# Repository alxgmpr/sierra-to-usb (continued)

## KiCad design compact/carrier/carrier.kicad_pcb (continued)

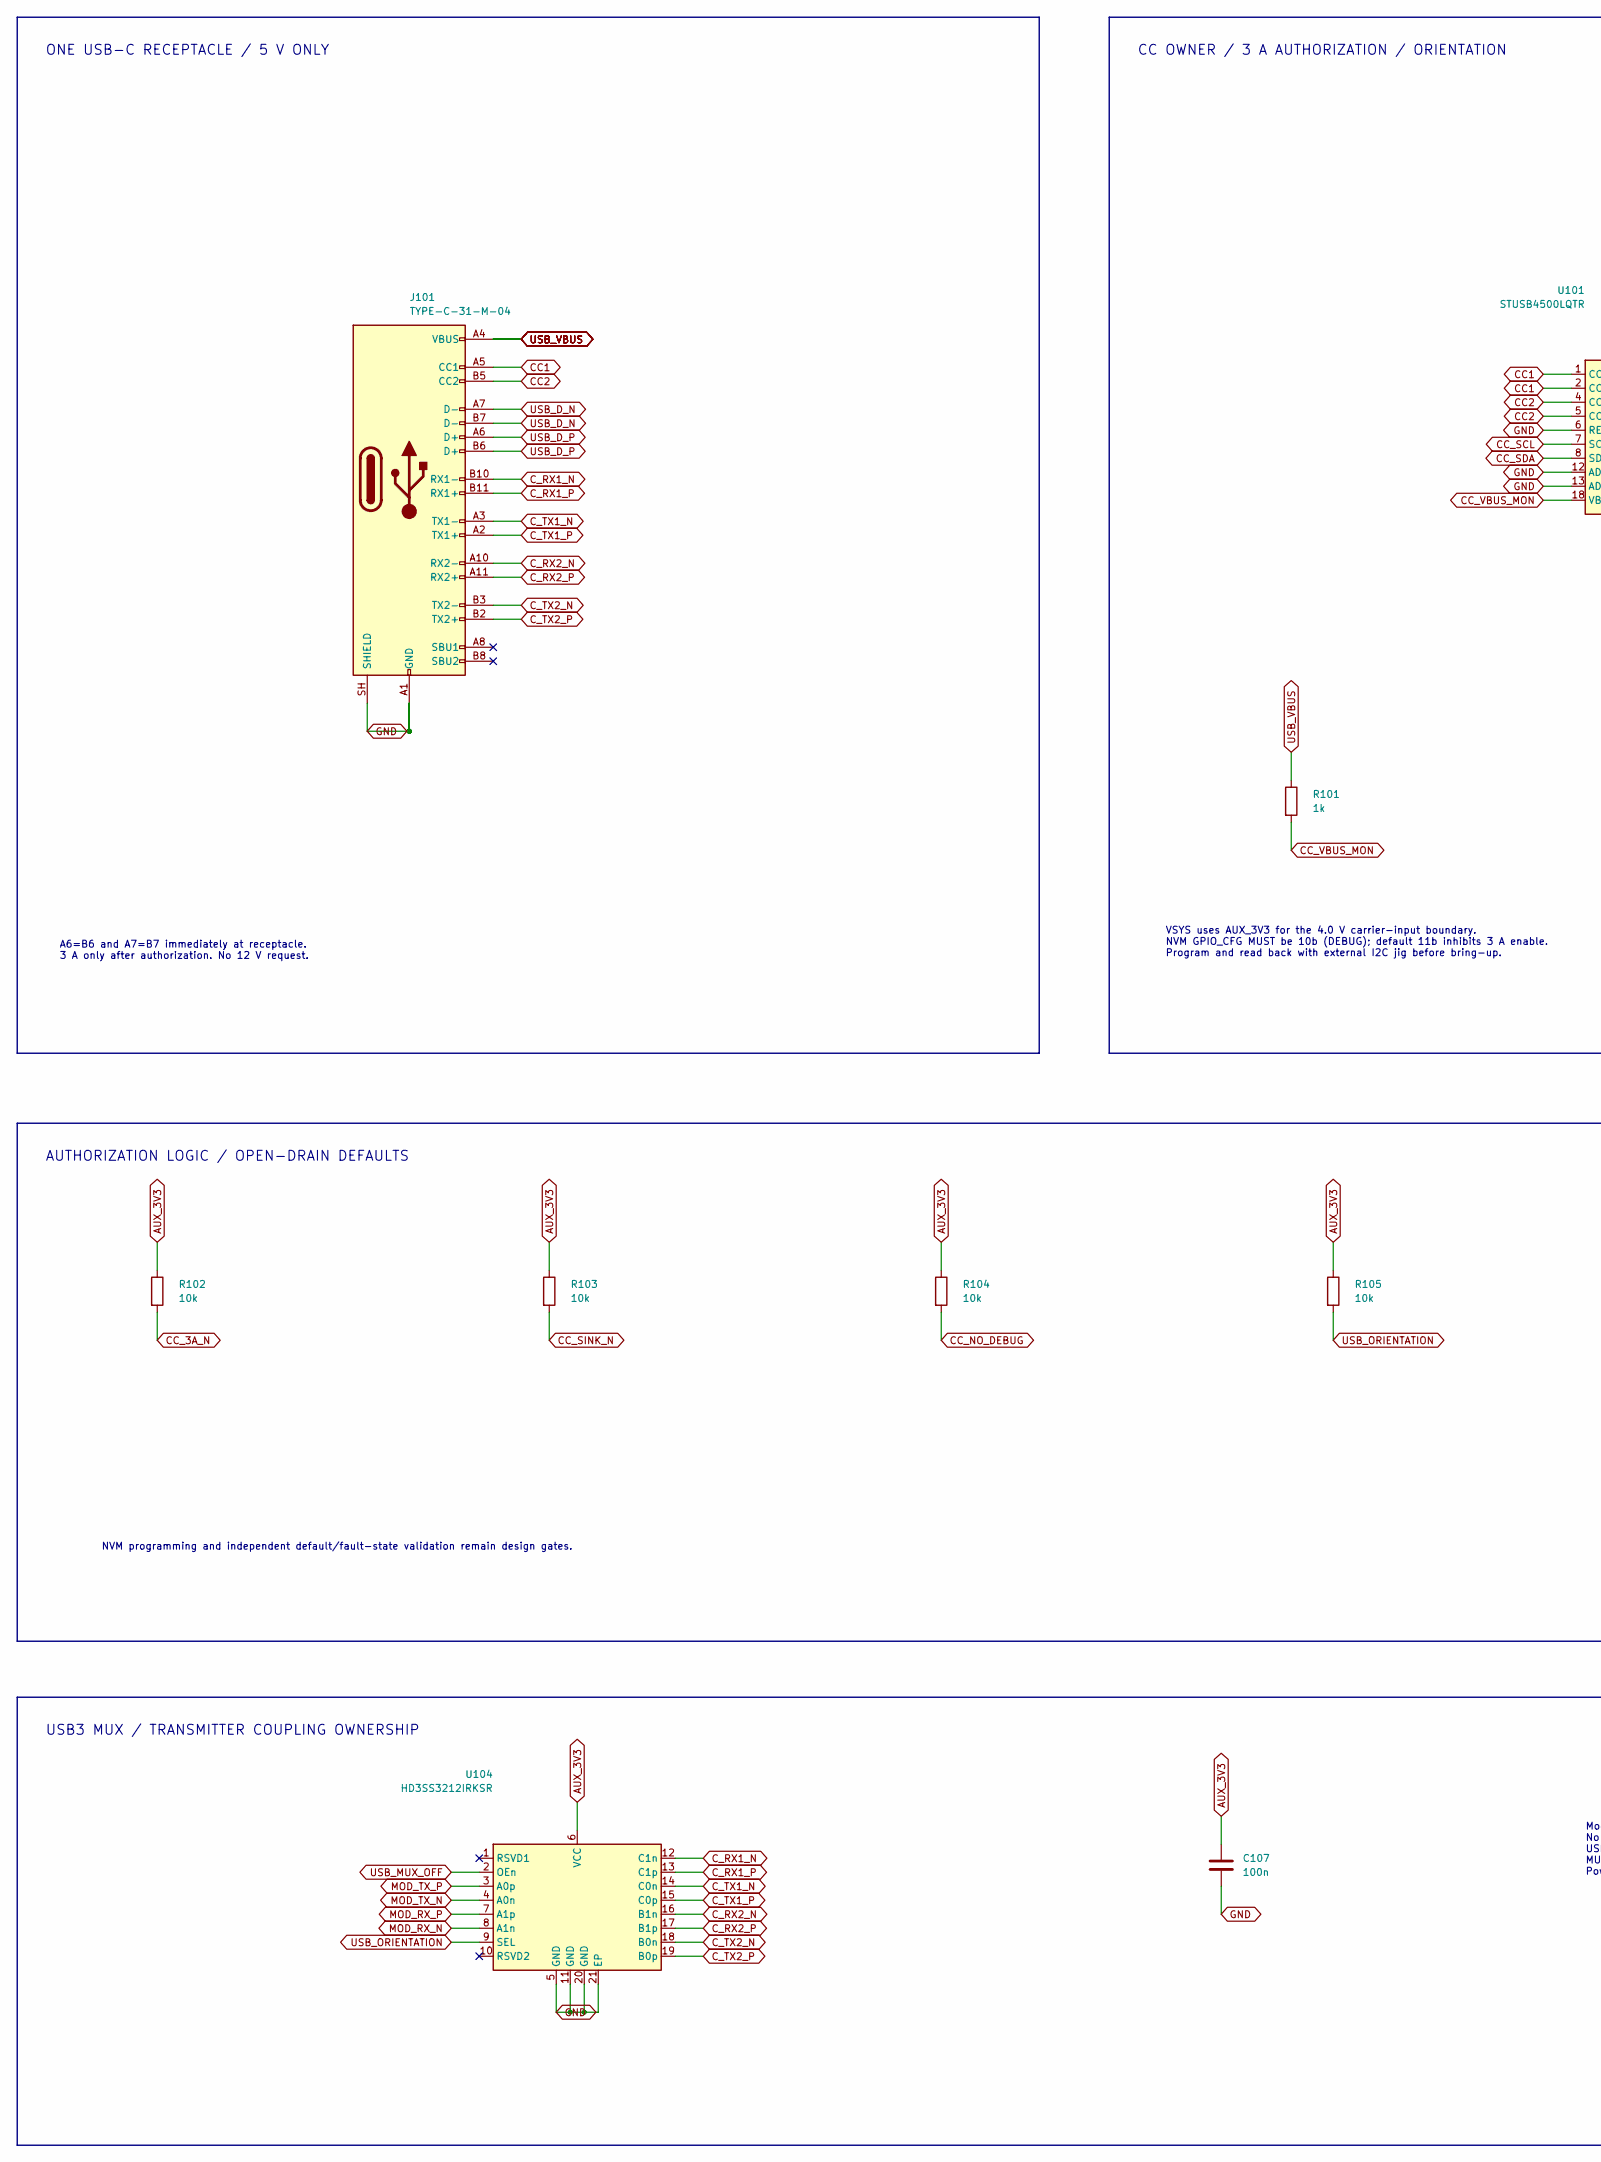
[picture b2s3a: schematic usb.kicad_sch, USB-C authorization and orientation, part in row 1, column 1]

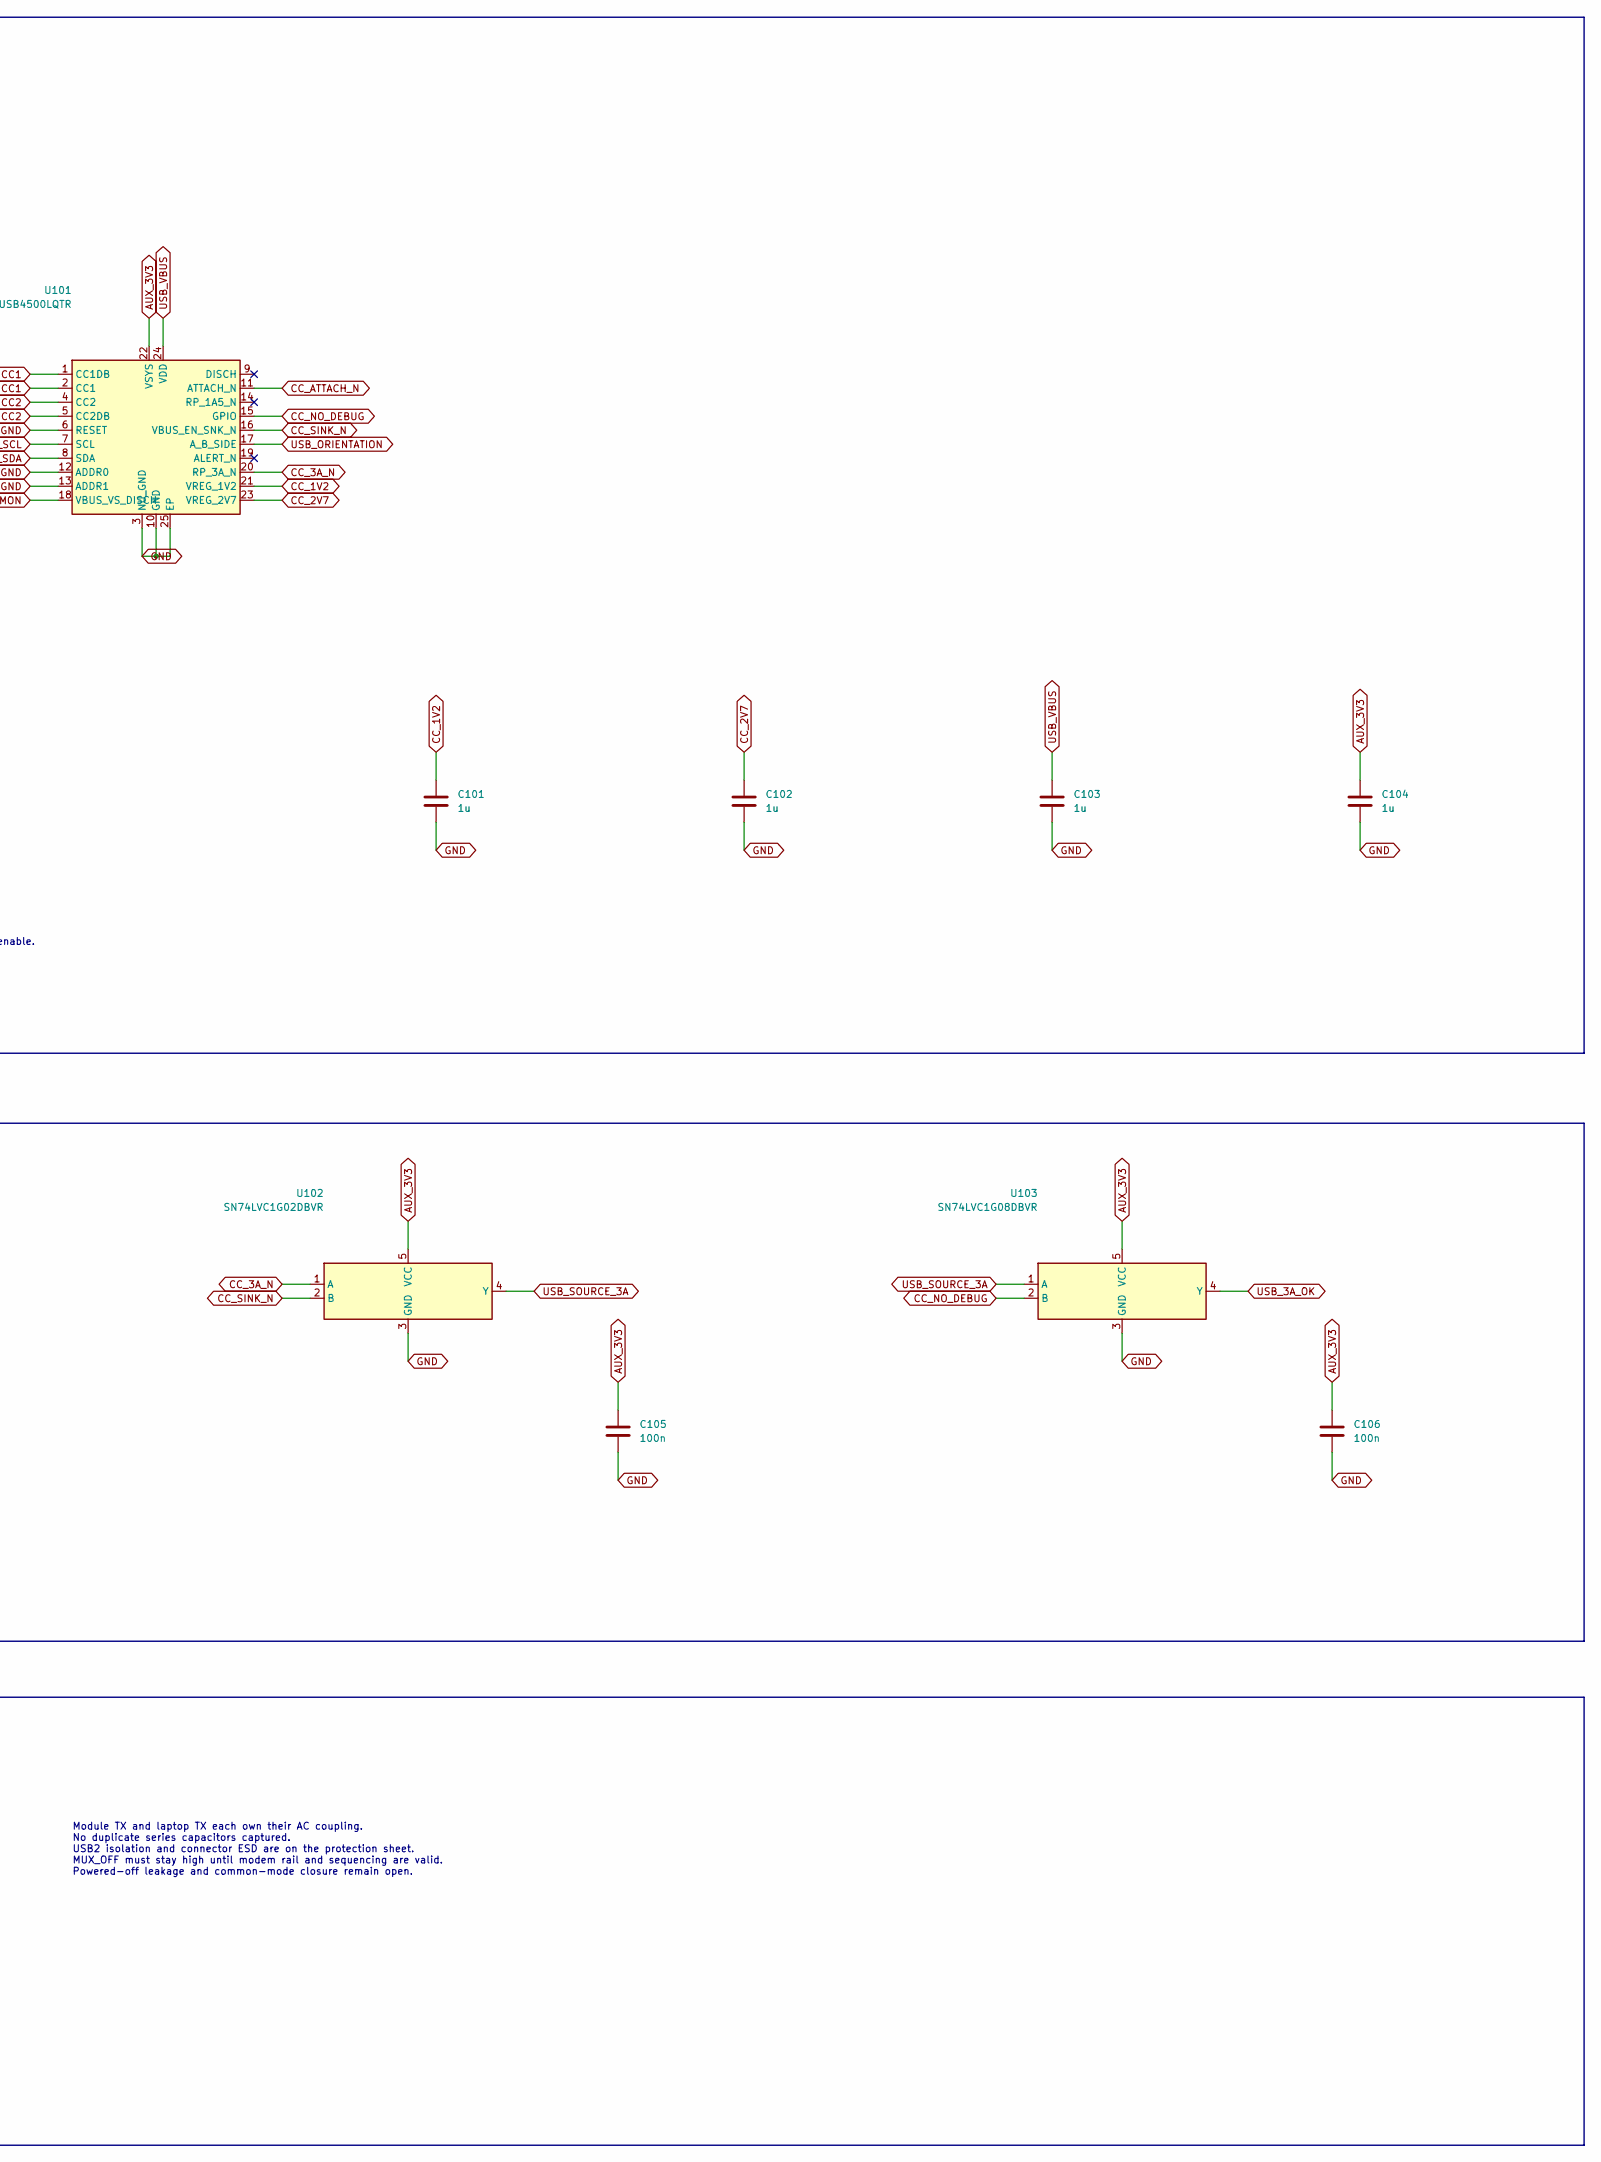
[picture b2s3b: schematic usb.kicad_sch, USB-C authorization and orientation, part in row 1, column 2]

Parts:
C101, C102, C103, C104: 1u; C_1206_3216Metric; MPN C3216X7R1H105K160AB
C105, C106, C107: 100n; C_0805_2012Metric; MPN C2012X7R1H104K085AA
J101: TYPE-C-31-M-04; USB_C_Receptacle_HRO_TYPE-C-31-M-04; MPN TYPE-C-31-M-04; LCSC C129018
R101: 1k; R_0603_1608Metric; MPN RC0603FR-071KL
R102, R103, R104, R105: 10k; R_0603_1608Metric; MPN RC0603FR-0710KL
U101: STUSB4500LQTR; QFN-24-1EP_4x4mm_P0.5mm_EP2.6x2.6mm; MPN STUSB4500LQTR
U102: SN74LVC1G02DBVR; SOT-23-5; MPN SN74LVC1G02DBVR
U103: SN74LVC1G08DBVR; SOT-23-5; MPN SN74LVC1G08DBVR
U104: HD3SS3212IRKSR; WQFN-20-1EP_2.5x4.5mm_P0.5mm_EP1x2.9mm; MPN HD3SS3212IRKSR

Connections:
AUX_3V3: C104.1, C105.1, C106.1, C107.1, R102.1, R103.1, R104.1, R105.1, U101.22 (VSYS), U102.5 (VCC), U103.5 (VCC), U104.6 (VCC); also elsewhere on the board
CC1: J101.A5 (CC1), U101.1 (CC1DB), U101.2 (CC1); also elsewhere on the board
CC2: J101.B5 (CC2), U101.4 (CC2), U101.5 (CC2DB); also elsewhere on the board
CC_1V2: C101.1, U101.21 (VREG_1V2)
CC_2V7: C102.1, U101.23 (VREG_2V7)
CC_3A_N: R102.2, U101.20 (RP_3A_N), U102.1 (A)
CC_ATTACH_N: U101.11 (ATTACH_N); also elsewhere on the board
CC_NO_DEBUG: R104.2, U101.15 (GPIO), U103.2 (B)
CC_SCL: U101.7 (SCL); also elsewhere on the board
CC_SDA: U101.8 (SDA); also elsewhere on the board
CC_SINK_N: R103.2, U101.16 (VBUS_EN_SNK_N), U102.2 (B)
CC_VBUS_MON: R101.2, U101.18 (VBUS_VS_DISCH)
C_RX1_N: J101.B10 (RX1-), U104.12 (C1n); also elsewhere on the board
C_RX1_P: J101.B11 (RX1+), U104.13 (C1p); also elsewhere on the board
C_RX2_N: J101.A10 (RX2-), U104.16 (B1n); also elsewhere on the board
C_RX2_P: J101.A11 (RX2+), U104.17 (B1p); also elsewhere on the board
C_TX1_N: J101.A3 (TX1-), U104.14 (C0n); also elsewhere on the board
C_TX1_P: J101.A2 (TX1+), U104.15 (C0p); also elsewhere on the board
C_TX2_N: J101.B3 (TX2-), U104.18 (B0n); also elsewhere on the board
C_TX2_P: J101.B2 (TX2+), U104.19 (B0p); also elsewhere on the board
GND: C101.2, C102.2, C103.2, C104.2, C105.2, C106.2, C107.2, J101.A1 (GND), J101.A12 (GND), J101.B1 (GND), J101.B12 (GND), J101.SH (SHIELD), U101.3 (NU_GND), U101.6 (RESET), U101.10 (GND), U101.12 (ADDR0), U101.13 (ADDR1), U101.25 (EP), U102.3 (GND), U103.3 (GND), U104.5 (GND), U104.11 (GND), U104.20 (GND), U104.21 (EP); also elsewhere on the board
MOD_RX_N: U104.8 (A1n); also elsewhere on the board
MOD_RX_P: U104.7 (A1p); also elsewhere on the board
MOD_TX_N: U104.4 (A0n); also elsewhere on the board
MOD_TX_P: U104.3 (A0p); also elsewhere on the board
USB_3A_OK: U103.4 (Y); also elsewhere on the board
USB_D_N: J101.A7 (D-), J101.B7 (D-); also elsewhere on the board
USB_D_P: J101.A6 (D+), J101.B6 (D+); also elsewhere on the board
USB_MUX_OFF: U104.2 (OEn); also elsewhere on the board
USB_ORIENTATION: R105.2, U101.17 (A_B_SIDE), U104.9 (SEL)
USB_SOURCE_3A: U102.4 (Y), U103.1 (A)
USB_VBUS: C103.1, J101.A4 (VBUS), J101.A9 (VBUS), J101.B4 (VBUS), J101.B9 (VBUS), R101.1, U101.24 (VDD); also elsewhere on the board

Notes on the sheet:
ONE USB-C RECEPTACLE / 5 V ONLY
A6=B6 and A7=B7 immediately at receptacle. 3 A only after authorization. No 12 V request.
CC OWNER / 3 A AUTHORIZATION / ORIENTATION
VSYS uses AUX_3V3 for the 4.0 V carrier-input boundary. NVM GPIO_CFG MUST be 10b (DEBUG); default 11b inhibits 3 A enable. Program and read back with external I2C jig before bring-up.
AUTHORIZATION LOGIC / OPEN-DRAIN DEFAULTS
NVM programming and independent default/fault-state validation remain design gates.
USB3 MUX / TRANSMITTER COUPLING OWNERSHIP
Module TX and laptop TX each own their AC coupling. No duplicate series capacitors captured. USB2 isolation and connector ESD are on the protection sheet. MUX_OFF must stay high until modem rail and sequencing are valid. Powered-off leakage and common-mode closure remain open.

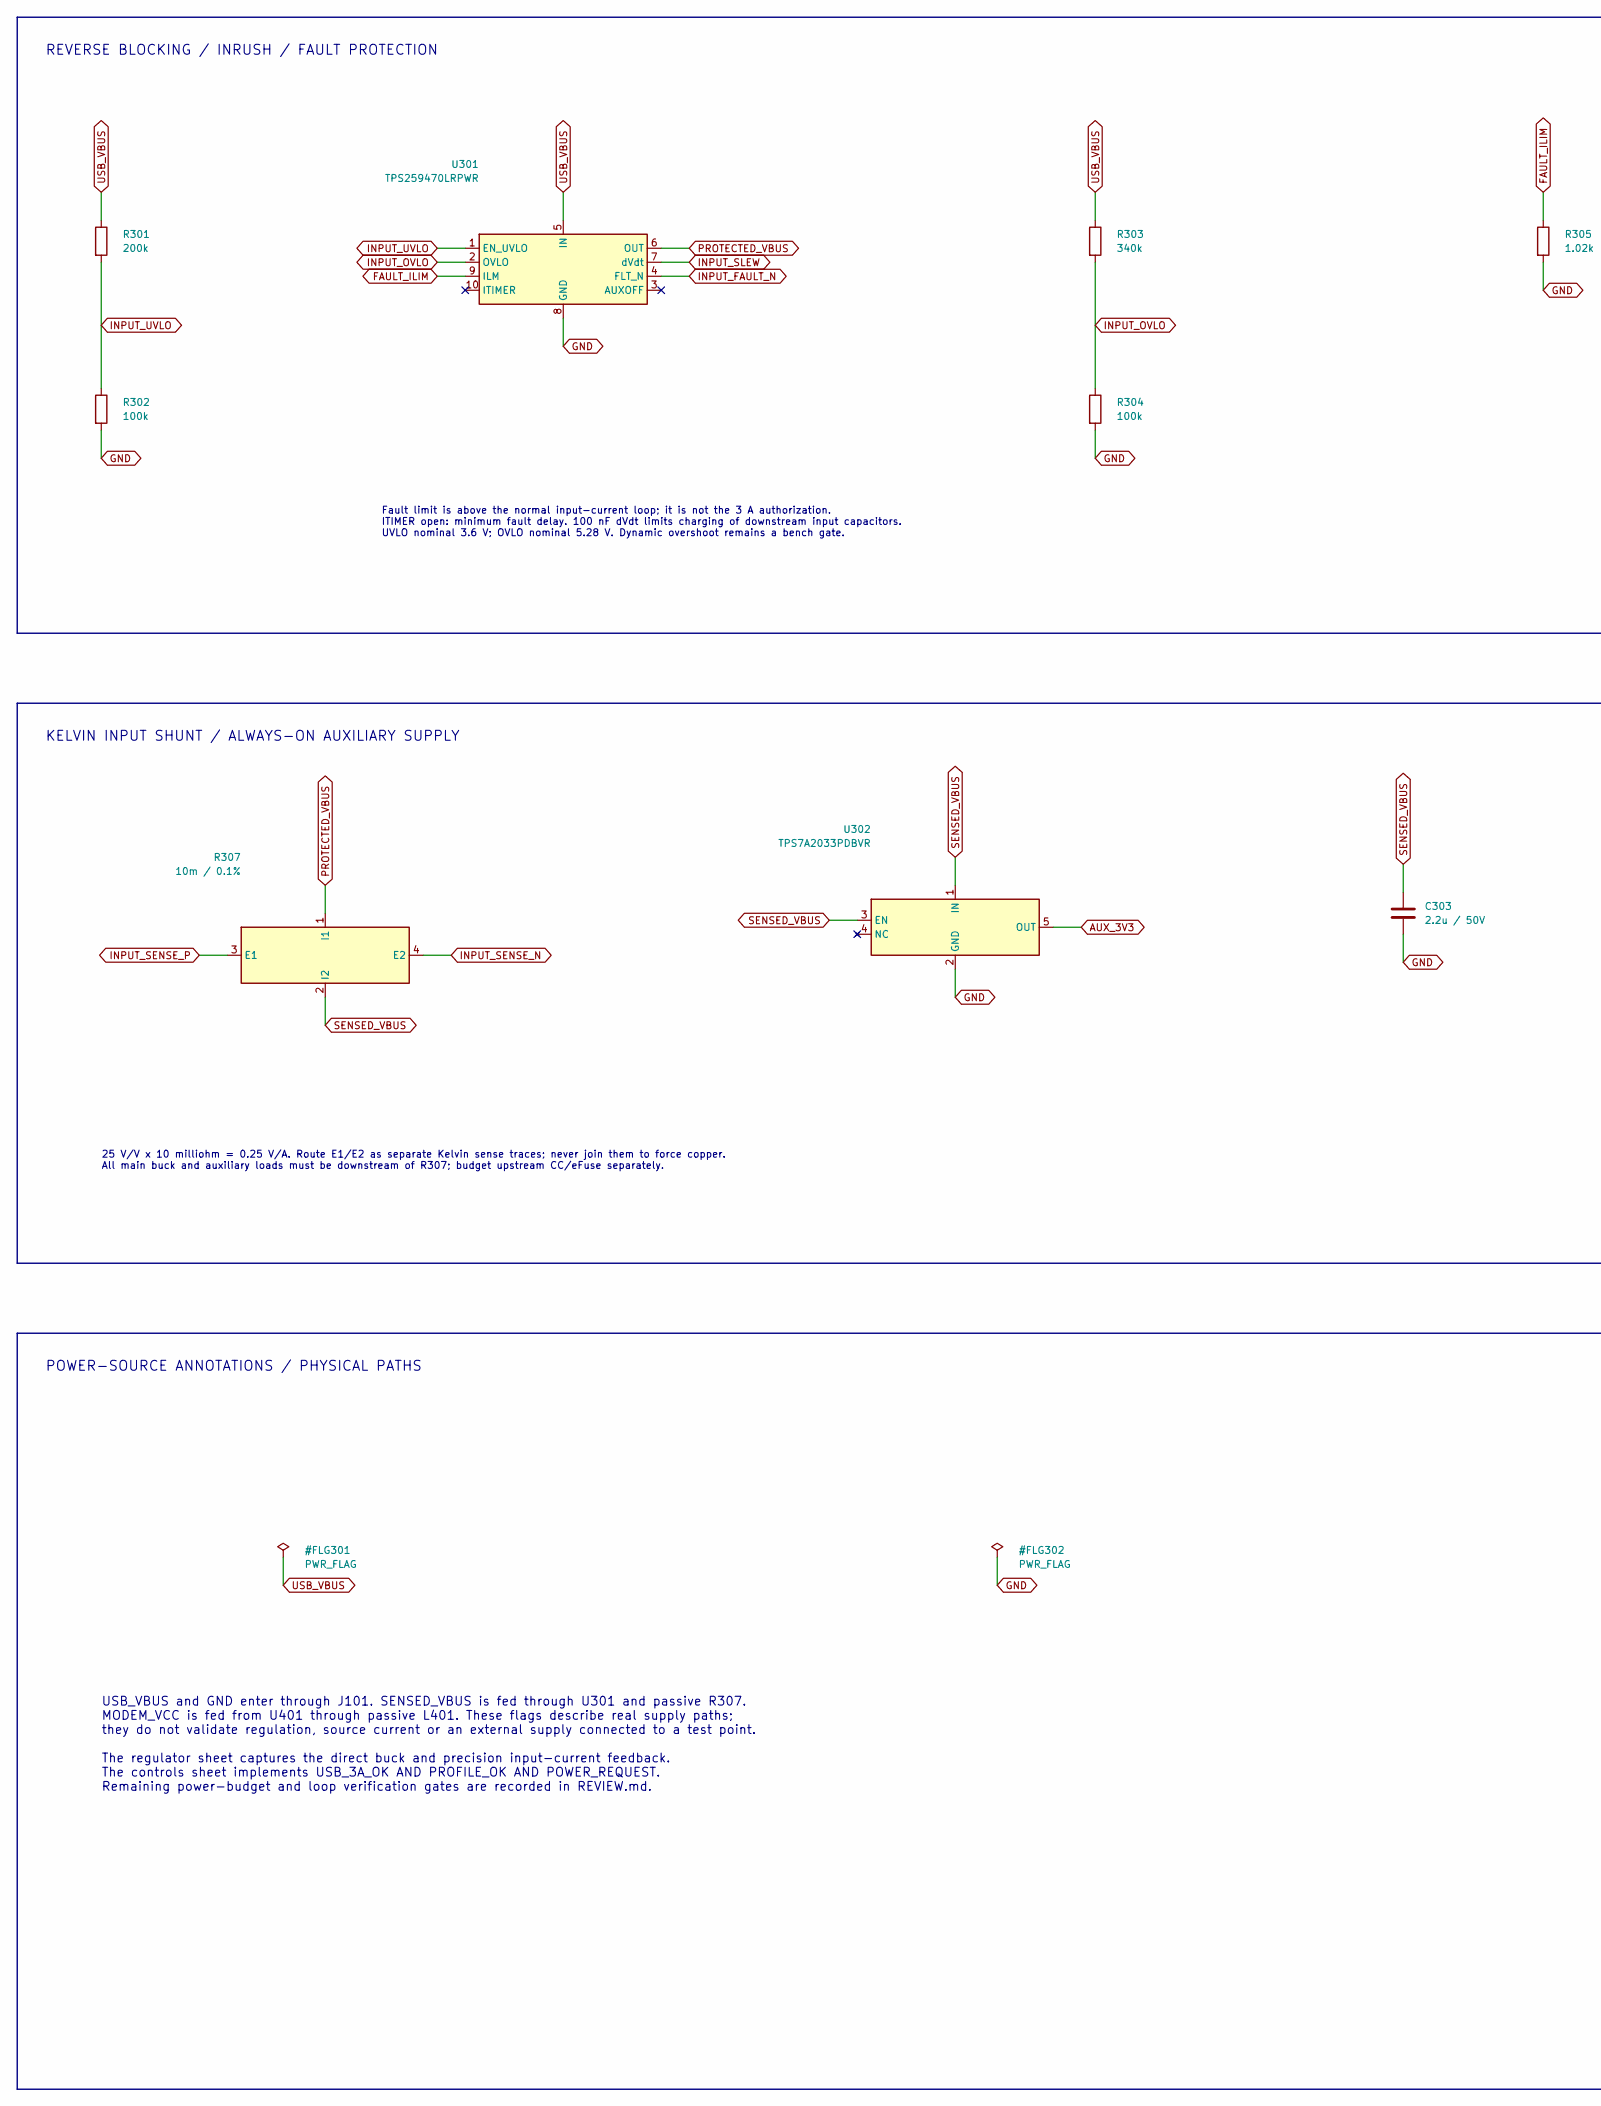
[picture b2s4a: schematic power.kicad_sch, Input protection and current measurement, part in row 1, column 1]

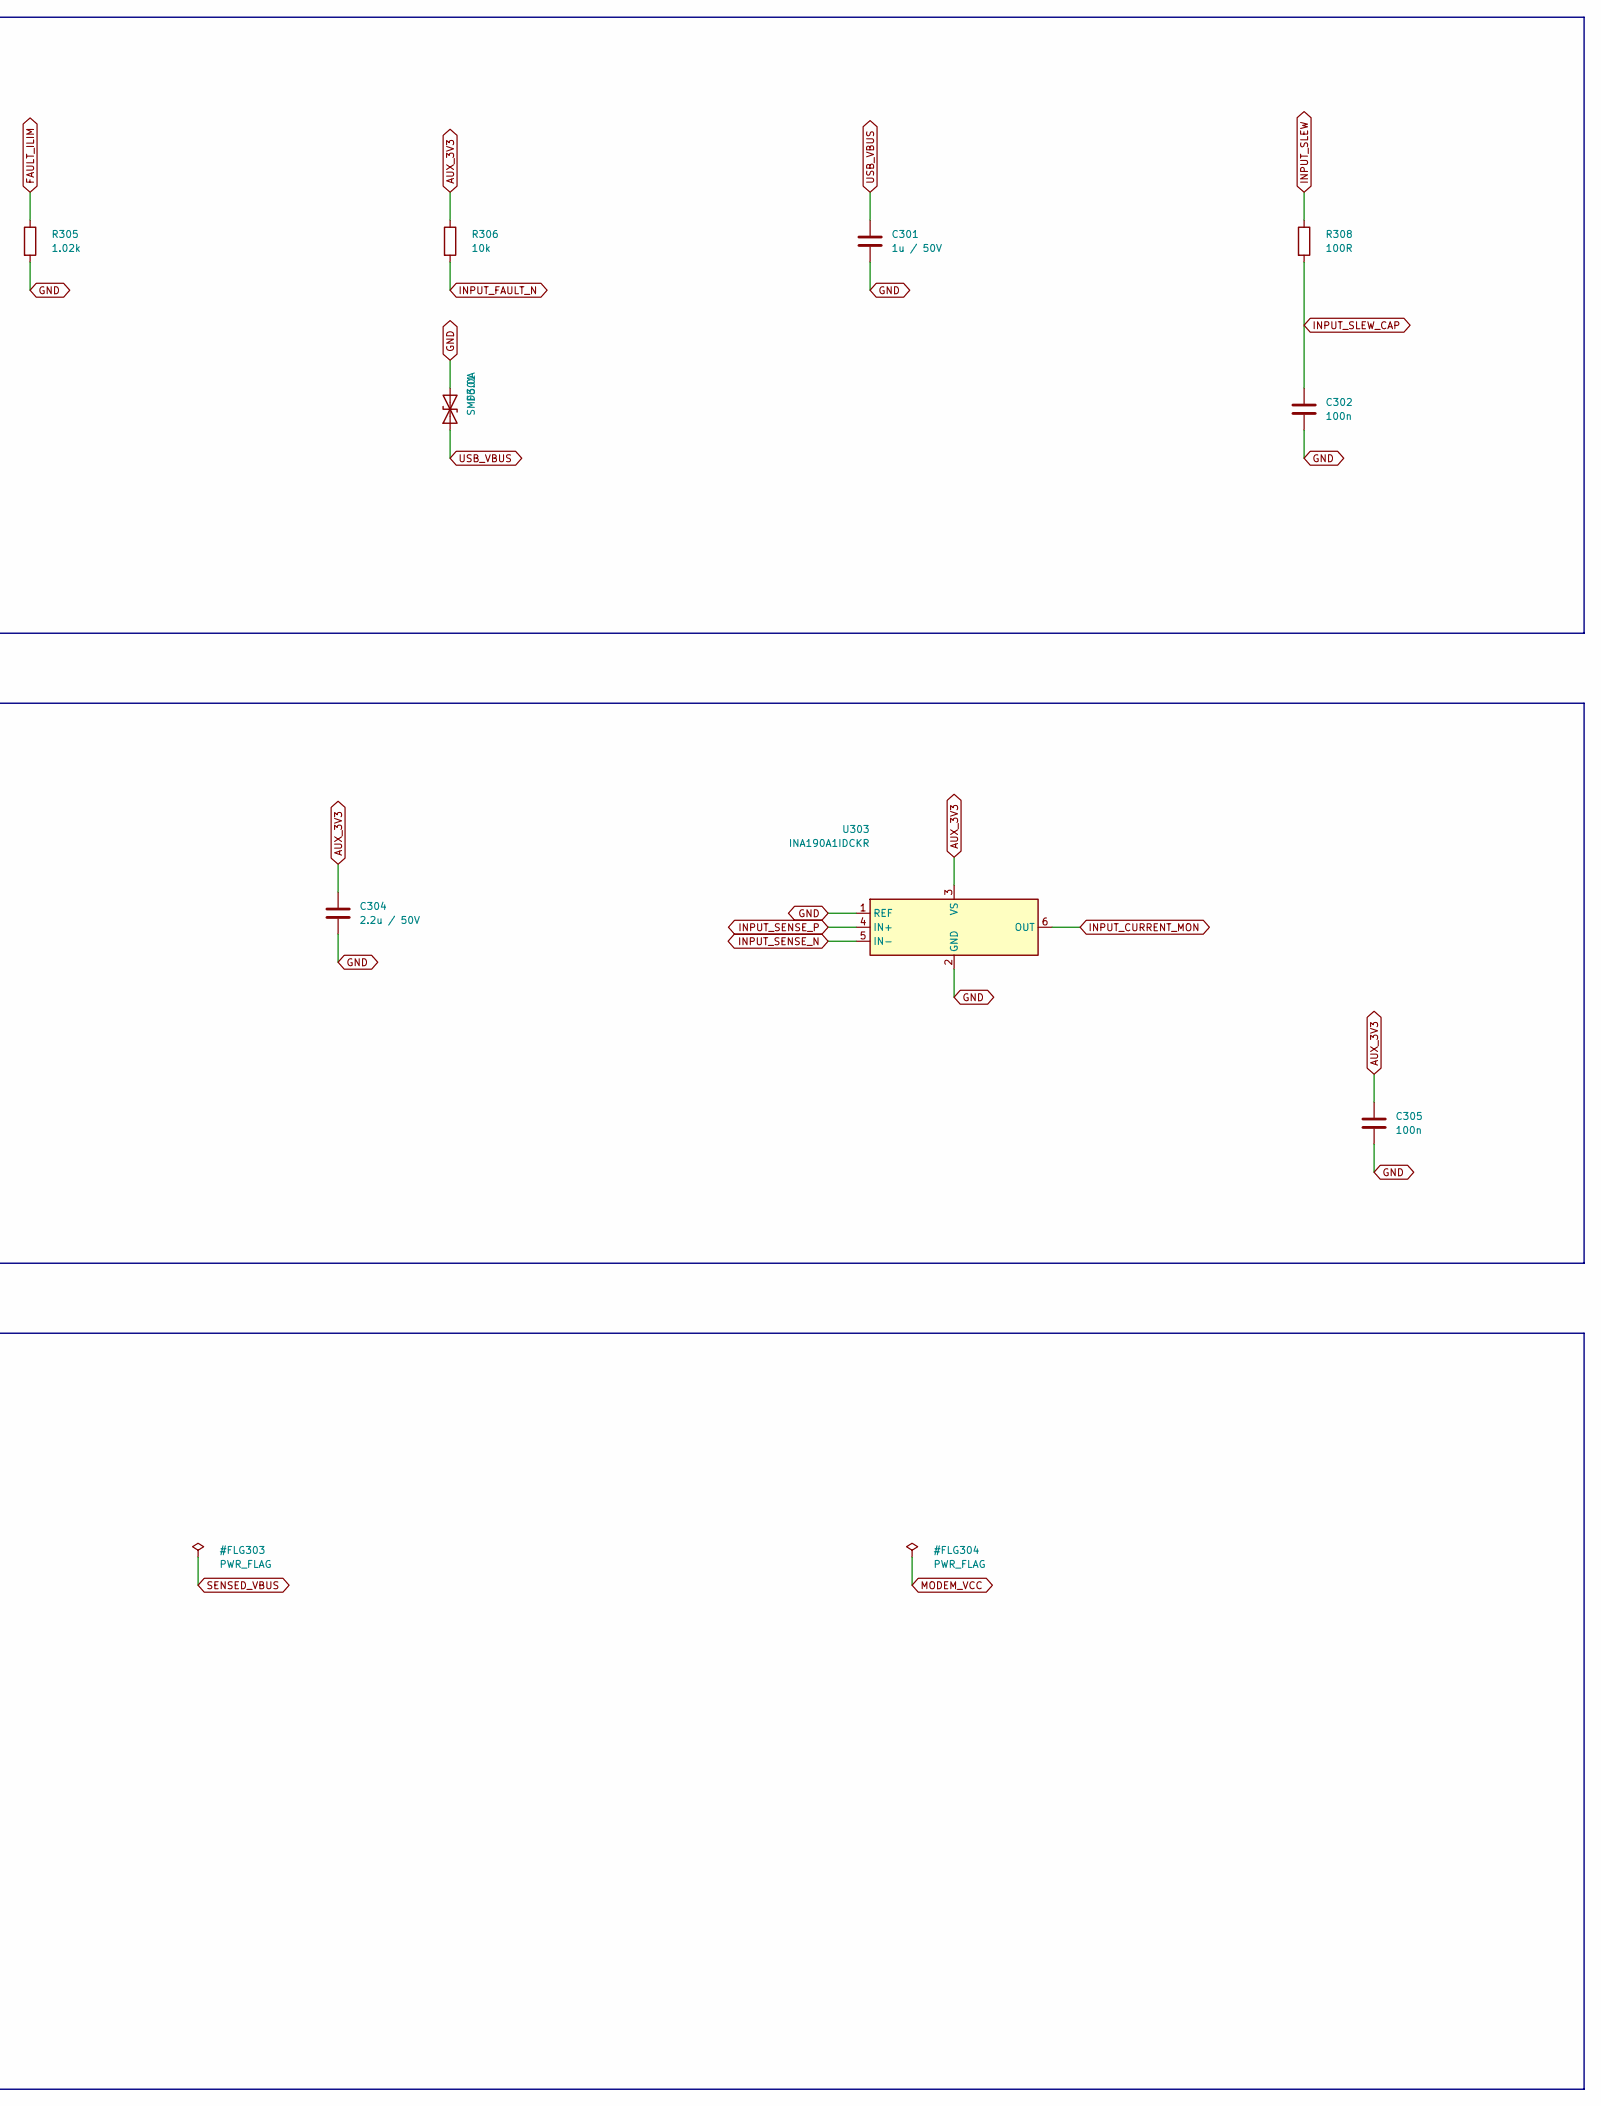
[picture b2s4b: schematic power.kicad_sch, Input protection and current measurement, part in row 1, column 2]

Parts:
C301: 1u / 50V; C_1206_3216Metric; MPN C3216X7R1H105K160AB
C302, C305: 100n; C_0805_2012Metric; MPN C2012X7R1H104K085AA
C303, C304: 2.2u / 50V; C_1206_3216Metric; MPN C3216X7R1H225K160AB
D301: SMF6.0A; Littelfuse_SMF_SOD123FL; MPN SMF6.0A
R301: 200k; R_0603_1608Metric; MPN ERJ-3EKF2003V
R302, R304: 100k; R_0603_1608Metric; MPN RC0603FR-07100KL
R303: 340k; R_0603_1608Metric; MPN RC0603FR-07340KL
R305: 1.02k; R_0603_1608Metric; MPN RC0603FR-071K02L
R306: 10k; R_0603_1608Metric; MPN RC0603FR-0710KL
R307: 10m / 0.1%; VPG_CSM2512_Kelvin; MPN Y14870R01000B9R
R308: 100R; R_0603_1608Metric; MPN RC0603FR-07100RL
U301: TPS259470LRPWR; TI_RPW0010A; MPN TPS259470LRPWR
U302: TPS7A2033PDBVR; SOT-23-5; MPN TPS7A2033PDBVR
U303: INA190A1IDCKR; SOT-363_SC-70-6; MPN INA190A1IDCKR

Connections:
AUX_3V3: C304.1, C305.1, R306.1, U302.5 (OUT), U303.3 (VS); also elsewhere on the board
FAULT_ILIM: R305.1, U301.9 (ILM)
GND: C301.2, C302.2, C303.2, C304.2, C305.2, D301.2 (A2), R302.2, R304.2, R305.2, U301.8 (GND), U302.2 (GND), U303.1 (REF), U303.2 (GND); also elsewhere on the board
INPUT_CURRENT_MON: U303.6 (OUT); also elsewhere on the board
INPUT_FAULT_N: R306.2, U301.4 (FLT_N)
INPUT_OVLO: R303.2, R304.1, U301.2 (OVLO)
INPUT_SENSE_N: R307.4 (E2), U303.5 (IN-)
INPUT_SENSE_P: R307.3 (E1), U303.4 (IN+)
INPUT_SLEW: R308.1, U301.7 (dVdt)
INPUT_SLEW_CAP: C302.1, R308.2
INPUT_UVLO: R301.2, R302.1, U301.1 (EN_UVLO)
PROTECTED_VBUS: R307.1 (I1), U301.6 (OUT)
SENSED_VBUS: C303.1, R307.2 (I2), U302.1 (IN), U302.3 (EN); also elsewhere on the board
USB_VBUS: C301.1, D301.1 (A1), R301.1, R303.1, U301.5 (IN); also elsewhere on the board

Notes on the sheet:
REVERSE BLOCKING / INRUSH / FAULT PROTECTION
Fault limit is above the normal input-current loop; it is not the 3 A authorization. ITIMER open: minimum fault delay. 100 nF dVdt limits charging of downstream input capacitors. UVLO nominal 3.6 V; OVLO nominal 5.28 V. Dynamic overshoot remains a bench gate.
KELVIN INPUT SHUNT / ALWAYS-ON AUXILIARY SUPPLY
25 V/V x 10 milliohm = 0.25 V/A. Route E1/E2 as separate Kelvin sense traces; never join them to force copper. All main buck and auxiliary loads must be downstream of R307; budget upstream CC/eFuse separately.
POWER-SOURCE ANNOTATIONS / PHYSICAL PATHS
USB_VBUS and GND enter through J101. SENSED_VBUS is fed through U301 and passive R307. MODEM_VCC is fed from U401 through passive L401. These flags describe real supply paths; they do not validate regulation, source current or an external supply connected to a test point. The regulator sheet captur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
